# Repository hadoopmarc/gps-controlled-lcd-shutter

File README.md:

# gps-controlled-lcd-shutter

## Introduction

The GPS-controlled LCD shutter is used for photography of bright meteors. Traditionally, periodic shutters are applied in multi-station photography for aiding the calculation of the atmospheric trajectory and velocity of a meteoroid. The controlling system documented in this git repository adds 1 Hz time markers to the waveform driving an LCD shutter. These markers are synchronized with the highly accurate time signal of a GPS module. The markers function as additional reference points for comparing records from multiple stations. The technique was pioneered by the Ondřejov Observatory in the Czech Republic, see: [https://link.springer.com/article/10.1007/s11038-017-9511-z](https://link.springer.com/article/10.1007/s11038-017-9511-z).

The required pattern for obstructing the light passing through the camera lens is visible from the photograph below (courtesy of the Astronomical Institute of the Academy of Sciences of the Czech Republic).

## Reference design

When using an LCD shutter to realize the required pattern one needs an LCD opaqueness waveform represented as signal I in the figure below. The end of a long part of the meteor trail - or the rising edge of the first pulse of a pulse train in signal I - occurs a N + 2/32 seconds exactly.

The waveform required to drive the LCD shutter has both a 16 Hz signature for the periodic interruptions and a 1 Hz signature for the second markers. The Ublox Neo-M8T SoC is able to deliver both signals with high precision on its TIMEPULSE and TIMEPULSE2 outputs (signals A and B). Because of this high precision, the design with Neo-M8T is designated as the reference design.

Apart from the frequencies involved, there are additional requirements for driving an LCD shutter:

- although an LCD shutter becomes opaque when a voltage is put on it in either direction, it is advised to change the polarity of the applied voltage with each cycle to avoid degradation of the display (signal H)
- upon switching, the shutter draws a relatively high peak current of 28 mA during a short time

These requirements make that the LCD-shutter is better not driven by logical outputs directly. Rather, the reference design applies opamps to convert the logical signals into +/- 12V with a sufficiently low output impedance, see the top part of the electronic circuit below. The final opamp adds the inverted signal F to the signal G to create signal H. The electronic circuit for the final opamp includes a variable resistor RV1 to set the "inactive" output voltage to exactly 0V for maximum transparency of the LCD shutter.

For converting signals A and B into signals F and G, a few CMOS NAND ports and a D-flipflop are applied. Note that the 1 Hz signal is also fed into the reset port of the flipflop to have the edges of the 8 Hz signals D and E coincide with the rising edge of the 1 Hz signal.

## Optimized design

Although the reference design guarantees a high timing precision, it has significant drawbacks:

- the Neo-M8T is 10 times more expensive than its more nimble Neo-M8N sibling and dominates the production costs of the system
- the Neo-M8T is not available on a breakout board with the TIMEPULSE and TIMEPULSE2 output signals, so this requires high-precision soldering on 1 mm spaced SMD output pins
- the opamp circuit requires positive and negative power supplies
- the opamp circuit is hard to get stable and can only barely supply the peak current of the LCD shutter

Presenting the reference design to two different audiences resulted in valuable feedback to optimize the design:

- the required waveforms can also be produced by a microcontroller such as the Arduino board, by only using the 1 Hz output signal of a GPS module and using the internal, less precise clock of the microcontroller to obtain the 16 Hz timing information (see [this contribution to the repository](https://github.com/hadoopmarc/gps-controlled-lcd-shutter/commit/29299f46e7cd1bd2d8dd73f03644191cccfc6193)). Now, the cheaper Neo-M8N suffices to provide the 1 Hz timing data.
- an H-bridge module - often used to drive a DC motor - seems also suitable to drive the LCD shutter. An H-bridge only requires a positive power supply and can deliver high output currents.

This feedback resulted in the final optimized design, displayed in the electronic circuit diagram below. As the LCD shutter is already driven with a 16 Hz frequency, the H-bridge PWM duty cycle has a fixed setting of 100%. An H-bridge has two modes for a low output voltage, see the truth table below: short circuit the output pins ("Short brake" in motor terms) or disconnect the output pins ("Free run until frictional stop" in motor terms). It turns out that the LCD shutter needs the short circuit so that it can release its internal charge/polarity and become transparent as fast as possible.

The required input signals to the H-bridge are displayed in the waveform diagram below. Also in this design, the end of a long segment in the meteor trail - or the rising edge of the first pulse of a pulse train in the LCD opacity signal - occurs a N + 2/32 seconds exactly. After all, the long segment in the meteor trail has a duration of 3/32 second, but the GPS second pulse occurs after 1/32 second from the start of the long segment.

## Validation of the designs

Proper operation of both designs can be validated with an [Arduino Oscilloscope](./doc/arduino-scope.md) and the small LED + phototransistor setup of the lower left part of the electronic circuit diagram.

The two oscilloscope diagrams above display signals F and G (yellow lines) simultaneously measured with the Pulse Per Second signal of the Neo-M8T module  (configured with a pulse duration of 50 ms). The pulse duration of signals F and G is 46875 ms (16 Hz with a duty cycle of 75% in case of a missing GPS satellite lock). The first diagram shows that the pulse at the start of a second is missing, as required.

In this image the yellow line represents the light throughput of the LCD shutter while driven by the reference design. The light is interrupted (sharp falling edges) at the start of a driver pulse (pulses not visible). There is no sharp falling edge coinciding with the rising edge of the GPS Pulse Per Second signal and the shutter can fully open. Note that these measurements were made with the cheap first generation LC-TEC shutters and that the measured opening response is consistent with [Figure 8.6 of their specifications](https://www.lc-tec.se/wp-content/uploads/2019/05/FOS_FOS-AR-specification-1602.pdf). Also note that the light transmission of the odd and even pulses is not exactly equal, indicating that the opamp driver circuit is not exactly balanced.

Again the light throughput against the GPS Pulse Per Second signal, but now for the optimized design with a Neo-M8N GPS module, an Arduino Nano and an H-bridge. Now, the GPS pulse has a duration of 100 ms and the duty cycle of the driver pulses is 50%, which gives the LCD-shutter more time to open than in the earlier image for the reference design.

This picture looks boring, but its significance is high. It displays the reference and optimized designs operating simultaneously with independent GPS receiver modules, both with a satellite lock. The white line shows signal F from the reference design, while the yellow line shows the H-bridge IN1 signal of the optimized design. This demonstrates that within the measuring accuracy of the oscilloscope used, the edges of the signals coincide.

This picture is a more attractive-looking variation on the picture above, again combining measurements from two independently operating setups. Here, signal F from the reference design (white line) is combined with the light throughput of the LCD shutter driven by the optimized design (yellow line). Also, here the opening and closing instances of the LCD-shutter nicely coincide with the falling and rising edges of signal F. Note that the measurements in the last two images were made with the electronic circuits built on a printed circuit board, while previous more noisy images were from circuits built on a breadboard. Also, a different phototransistor and LCD-shutter were used, explaining the slightly different light throughput curve, compared to the earlier images.

Starting from version 0.2.0 the electrical shut percentage can be configured to compensate for LCD shutters that fail to reopen fast enough to truthfully follow the electrical signals. In this oscilloscope screenshot a shut percentage of 25% is applied to a cheap LCD shutter, resulting in an open/closed ratio of roughly 50/50. White line is the GPS signal.

## Phase measurements in the optimized design

Apart from validation measurements of the output signals of the electronic circuits, it is also possible to use internal measurements from the microcontroller as a form of validation. The controlling software generates the pulses using timer interrupts. The timer period is chosen such that the end of a pulse train occurs at a phase difference Δt just before the ideal time instance required by the nanosecond precision GPS time. For an Arduino Nano microcontroller the timer has a limited resolution and as a result Δt has a stable value between 0 and 128 microseconds. How to monitor this phase difference and phase stability is described [here](./doc/arduino-programming.md).

## Further documentation

- [Programming the Arduino Nano module](./doc/arduino-programming.md)
- [Measuring with an Arduino Oscilloscope](./doc/arduino-scope.md)
- [Datasheets of system components](./doc/datasheet.md)

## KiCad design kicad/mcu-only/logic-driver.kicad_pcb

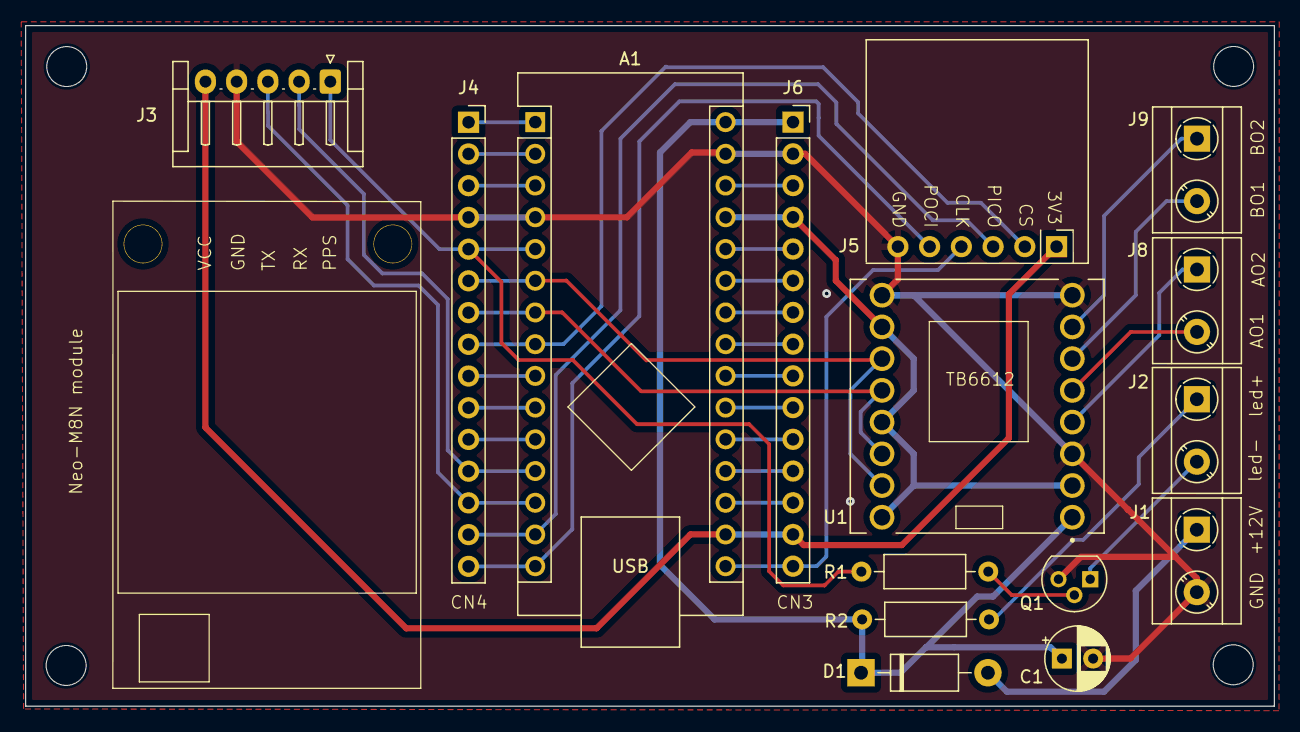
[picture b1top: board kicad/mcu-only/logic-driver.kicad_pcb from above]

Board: 2 copper layers, 100.0 x 54.5 mm, 19 parts (0 on the bottom side), 37 nets.

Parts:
A1: STM32G431 / Arduino Nano; Arduino_Nano
C1: 47uF; CP_Radial_D5.0mm_P2.50mm
D1: 1N5818; D_DO-41_SOD81_P10.16mm_Horizontal
H1, H2, H3, H4: Hole; MountingHole_3.2mm_M3_ISO14580
J1: 12V/1A power in; TerminalBlock_RND_1x02_P5.00mm_Horizontal_Small_Courtyard
J2: PPS; TerminalBlock_RND_1x02_P5.00mm_Horizontal_Small_Courtyard
J3: Onboard Neo_M8N; Neo-M8N_1x05_P2.50mm_Horizontal
J4: CN4; PinSocket_1x15_P2.54mm_Vertical
J5: Onboard SD-card; SDcard_IPC_breakout_1x06_P2.54mm_Vertical
J6: CN3; PinSocket_1x15_P2.54mm_Vertical
J8: LCD-A; TerminalBlock_RND_1x02_P5.00mm_Horizontal_Small_Courtyard
J9: LCD-B; TerminalBlock_RND_1x02_P5.00mm_Horizontal_Small_Courtyard
Q1: BC547; TO-92
R1: 47k; R_Axial_DIN0207_L6.3mm_D2.5mm_P10.16mm_Horizontal
R2: 1k5; R_Axial_DIN0207_L6.3mm_D2.5mm_P10.16mm_Horizontal
U1: ROB-14450; TB6612_Module_ROB-14450

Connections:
/+12V: A1.30 (VIN), C1.1, D1.1 (K), J6.1, R2.1, U1.1 (VM)
/AVDD: A1.18 (AREF), J6.13
/MCU_3V3: A1.17 (3V3), J3.5, J5.1, J6.14
/MCU_5V: A1.27 (+5V), J6.4, U1.2 (VCC), U1.10 (PWMB), U1.13 (STBY), U1.16 (PWMA)
/NRSTA: A1.3 (~RESET), J4.3
/NRSTB: A1.28 (~RESET), J6.3
/PA0: A1.19 (A0), J6.12
/PA1: A1.20 (A1), J6.11
/PA2: A1.26 (A7), J6.5
/PA3: A1.21 (A2), J6.10
/PA4: A1.22 (A3), J6.9
/PA5/PB7: A1.23 (SDA/A4), J6.8
/PA6/PA15: A1.24 (SCL/A5), J6.7
/PA7: A1.25 (A6), J6.6
/PA8: A1.12 (D9), J3.2, J4.12
/PA9: A1.1 (TX1), J4.1
/PA10: A1.2 (RX1), J4.2
/PA11: A1.13 (D10), J3.3, J4.13
/PA12: A1.5 (D2), J3.1, J4.5, R1.1
/PA15: A1.8 (D5), J4.8, J5.2
/PB0: A1.6 (D3), J4.6, U1.11 (BI2), U1.15 (AI2)
/PB3/PB8: A1.16 (SCK), J5.4, J6.15
/PB4: A1.15 (MISO), J4.15, J5.5
/PB5: A1.14 (MOSI), J4.14, J5.3
/PB6: A1.9 (D6), J4.9
/PB7: A1.7 (D4), J4.7, U1.12 (BI1), U1.14 (AI1)
/PF0: A1.10 (D7), J4.10
/PF1: A1.11 (D8), J4.11
GND: A1.4 (GND), A1.29 (GND), C1.2, J1.2, J3.4, J4.4, J5.6, J6.2, Q1.3 (E), U1.3 (GND), U1.8 (GND), U1.9 (GND)
unnamed: D1.2 (A), J1.1
unnamed: J2.1, R2.2
unnamed: J2.2, Q1.1 (C)
unnamed: J8.1, U1.4 (A01)
unnamed: J8.2, U1.5 (A02)
unnamed: J9.1, U1.7 (B01)
unnamed: J9.2, U1.6 (B02)
unnamed: Q1.2 (B), R1.2

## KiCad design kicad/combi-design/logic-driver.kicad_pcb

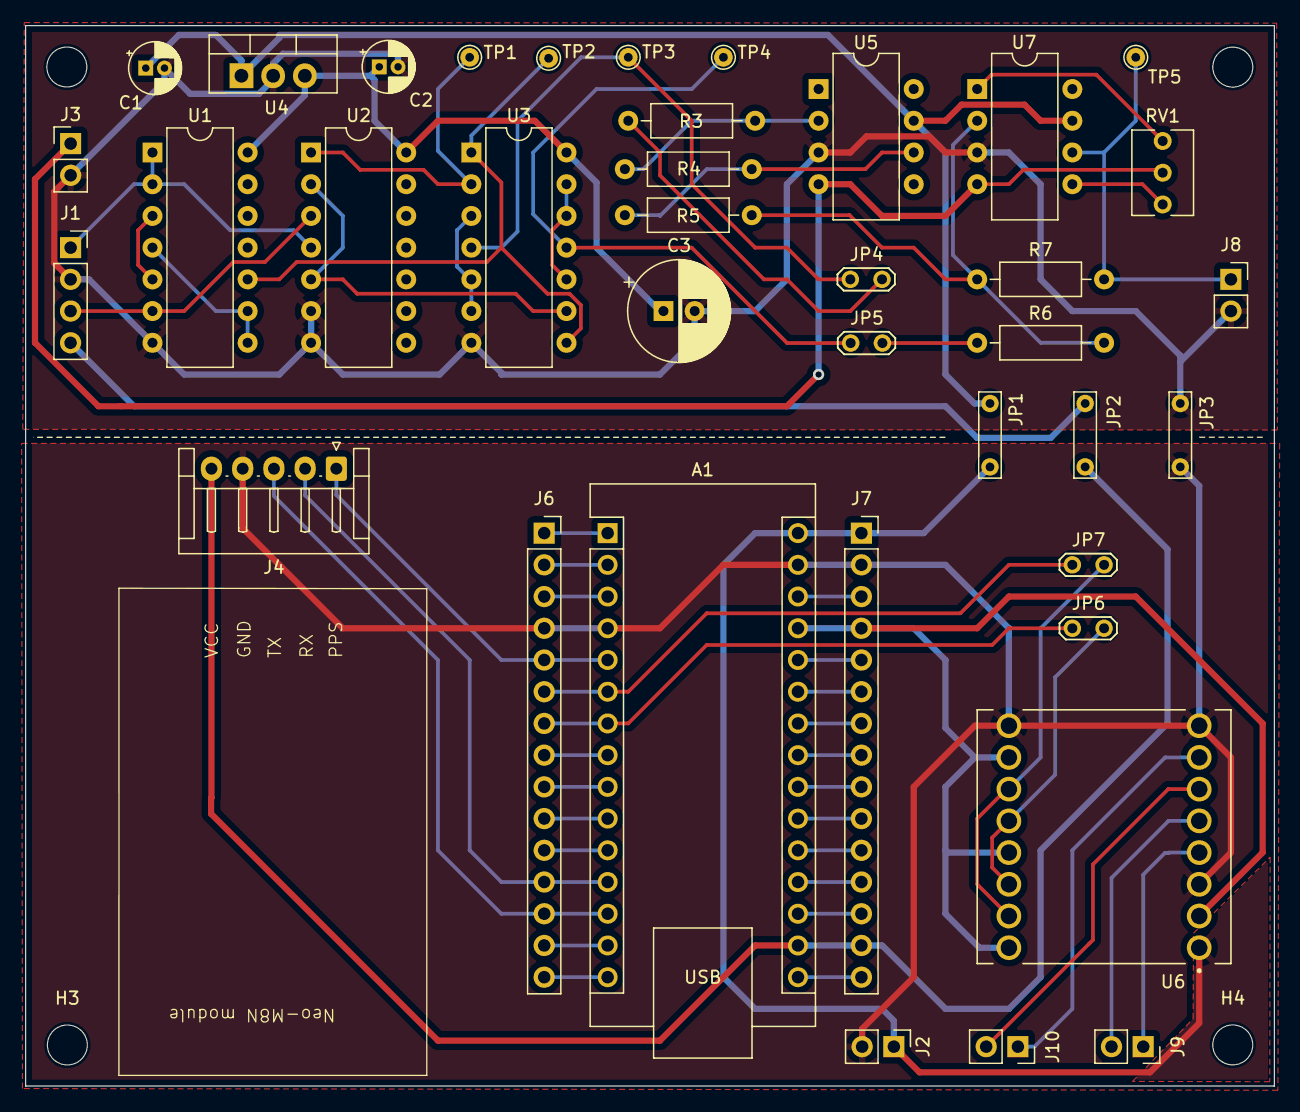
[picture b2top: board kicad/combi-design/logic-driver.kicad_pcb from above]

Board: 2 copper layers, 100.0 x 84.9 mm, 42 parts (0 on the bottom side), 59 nets.

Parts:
A1: Nucleo32-STM32G431; Arduino_Nano
C1, C2: 2.2uF; CP_Radial_D4.0mm_P1.50mm
C3: 100uF; CP_Radial_D8.0mm_P2.50mm
H1, H2, H3, H4: MountingHole; MountingHole_3.2mm_M3_ISO14580
J1: Neo-M8T; PinSocket_1x04_P2.54mm_Vertical
J2, J3: Power in; PinHeader_1x02_P2.54mm_Vertical
J4: Onboard Neo_M8N; Neo-M8N_1x05_P2.50mm_Horizontal
J6: CN4; PinSocket_1x15_P2.54mm_Vertical
J7: CN3; PinSocket_1x15_P2.54mm_Vertical
J8: LCD-opamp; PinSocket_1x02_P2.54mm_Vertical
J9: LCD-A; PinSocket_1x02_P2.54mm_Vertical
J10: LCD-B; PinSocket_1x02_P2.54mm_Vertical
JP1: +12V; TestPoint_Bridge_Pitch5.08mm_Drill0.7mm
JP2: +3V3; TestPoint_Bridge_Pitch5.08mm_Drill0.7mm
JP3: GND; TestPoint_Bridge_Pitch5.08mm_Drill0.7mm
JP4, JP6: Pos pulses; TestPoint_2Pads_Pitch2.54mm_Drill0.8mm
JP5, JP7: Neg pulses; TestPoint_2Pads_Pitch2.54mm_Drill0.8mm
R3, R4, R5, R6, R7: 100k; R_Axial_DIN0207_L6.3mm_D2.5mm_P10.16mm_Horizontal
RV1: 100k; Potentiometer_Vishay_T73XW_Horizontal
TP1: Signal D; TestPoint_THTPad_D1.5mm_Drill0.7mm
TP2: Signal C; TestPoint_THTPad_D1.5mm_Drill0.7mm
TP3: Signal F; TestPoint_THTPad_D1.5mm_Drill0.7mm
TP4: Signal G; TestPoint_THTPad_D1.5mm_Drill0.7mm
TP5: Signal H; TestPoint_THTPad_D1.5mm_Drill0.7mm
U1, U3: 4011; CERDIP-14_W7.62mm_SideBrazed
U2: 4013; CERDIP-14_W7.62mm_SideBrazed
U4: LM7805_TO220; TO-220-3_Vertical
U5, U7: TL081; CERDIP-8_W7.62mm_SideBrazed
U6: ROB-14450; TB6612_Module_ROB-14450

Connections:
+L12V: C1.1, JP1.2 (B), U4.1 (VI), U5.7 (V+), U7.7 (V+)
-L12V: J3.1, RV1.2, U5.4 (V-), U7.4 (V-)
/+5V: C2.1, C3.1, U1.14 (VDD), U2.14 (VDD), U3.14 (VDD), U4.3 (VO)
/+12V: A1.30 (VIN), J2.1, J7.1, JP1.1 (A), U6.1 (VM)
/AVDD: A1.18 (AREF), J7.13
/L3V3: J1.4, JP2.2 (B)
/LGND: C1.2, C2.2, C3.2, J1.2, J3.2, J8.2, JP3.2 (B), U1.7 (VSS), U2.6 (S), U2.7 (VSS), U3.7 (VSS), U4.2 (GND), U5.3 (+), U7.3 (+)
/MCU_3V3: A1.17 (3V3), J4.5, J7.14, JP2.1 (A)
/MCU_5V: A1.27 (+5V), J7.4, U6.2 (VCC), U6.10 (PWMB), U6.13 (STBY), U6.16 (PWMA)
/NRSTA: A1.3 (~RESET), J6.3
/NRSTB: A1.28 (~RESET), J7.3
/PA0: A1.19 (A0), J7.12
/PA1: A1.20 (A1), J7.11
/PA2: A1.26 (A7), J7.5
/PA3: A1.21 (A2), J7.10
/PA4: A1.22 (A3), J7.9
/PA5/PB7: A1.23 (SDA/A4), J7.8
/PA6/PA15: A1.24 (SCL/A5), J7.7
/PA7: A1.25 (A6), J7.6
/PA8: A1.12 (D9), J4.2, J6.12
/PA9: A1.1 (TX1), J6.1
/PA10: A1.2 (RX1), J6.2
/PA11: A1.13 (D10), J4.3, J6.13
/PA12: A1.5 (D2), J4.1, J6.5
/PA15: A1.8 (D5), J6.8
/PB0: A1.6 (D3), J6.6, JP7.1 (A)
/PB3/PB8: A1.16 (SCK), J7.15
/PB4: A1.15 (MISO), J6.15
/PB5: A1.14 (MOSI), J6.14
/PB6: A1.9 (D6), J6.9
/PB7: A1.7 (D4), J6.7, JP6.1 (A)
/PF0: A1.10 (D7), J6.10
/PF1: A1.11 (D8), J6.11
GND: A1.4 (GND), A1.29 (GND), J2.2, J4.4, J6.4, J7.2, JP3.1 (A), U6.3 (GND), U6.8 (GND), U6.9 (GND)
unnamed: J1.1, U1.1, U1.2, U2.4 (R)
unnamed: J1.3, U1.6, U2.3 (C)
unnamed: J8.1, R7.2, TP5.1, U7.6
unnamed: J9.1, U6.4 (A01)
unnamed: J9.2, U6.5 (A02)
unnamed: J10.1, U6.7 (B01)
unnamed: J10.2, U6.6 (B02)
unnamed: JP4.1 (A), TP3.1, U3.4
unnamed: JP4.2 (B), R3.1
unnamed: JP5.1 (A), TP4.1, U3.11
unnamed: JP5.2 (B), R6.1
unnamed: JP6.2 (B), U6.12 (BI1), U6.14 (AI1)
unnamed: JP7.2 (B), U6.11 (BI2), U6.15 (AI2)
unnamed: R4.2, R5.1, U5.6
unnamed: RV1.1, U7.1 (NULL)
unnamed: RV1.3, U7.5 (NULL)
unnamed: TP2.1, U1.10, U3.1, U3.8
unnamed: U1.3, U1.5
unnamed: U1.4, U1.8, U1.9
unnamed: U2.2 (~Q), U2.5 (D), U3.9
unnamed: TP1.1, U2.1 (Q), U3.2
unnamed: U3.3, U3.5, U3.6
unnamed: U3.10, U3.12, U3.13
unnamed: R3.2, R4.1, U5.2 (-)
unnamed: R5.2, R6.2, R7.1, U7.2 (-)

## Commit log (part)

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2023-11-28 Adds initial documentation and placeholder for Arduino script
2023-12-12 Added a script to generate the waveform
2023-12-12 just noticed it was supposed to be 16, not 32Hz
2023-12-13 Fixed the period being clipped to an int
    The period was being calculated as 62 instead of 62.5, resulting
    in subtle timing errors.
2023-12-28 Adds documentation on Neo-M8T configuration
2023-12-28 Fixes table rendering on github, first attempt
2023-12-28 Fixes table rendering on github, 2nd attempt
2023-12-28 Corrects 75% pulse duration without satfix
2023-12-29 Adds ublox config save command and some datasheets
2024-01-12 Rewires the D-flipflop divider to have signal C in phase with TIMEPULSE
2024-01-12 Puts arduino file in folder
2024-01-12 Adds Arduino oscilloscope files
2024-02-04 Adds two images
2024-02-04 Improves oscilloscope display
2024-02-04 Adds datasheet links
2024-02-17 Updates the electronic schema
2024-03-10 Adds unfinished Arduino R4 script for slow 3-level waveform on A0 DAC output
2024-03-10 Adds Arduino slow waveform with two dig outputs; still without timers
2024-03-17 Adds arduino script for measuring loop jitter
2024-03-22 Adds new Arduino test waveforms for attempts on faster opening the LCD-shutter
2024-04-01 Redesigns the main two-pin waveform, still with errors but promising
2024-04-08 Completes accurate waveform using two of three mechanisms
2024-04-13 Update schema regarding voltage follower
2024-05-05 Improves two pin waveform regarding stability and consistency
2024-05-05 Fixes logic error when to increment the iHalfWave counter
2024-05-09 Adds script for driving an H-bridge
2024-05-25 Adds rened kicad circuit and the kicad PCB design
2024-05-25 Updates electric circuit diagram
2024-06-08 Add documentation for programming the Arduino
2024-06-23 Adds documentation for measuring with the Arduino oscilloscope script
2024-06-29 Fixes overflow issue
2024-06-29 Updates arduino docs with the changed figures
2024-06-29 Fixes second marker for new iGpsPulse semantics + cleaning up
2024-06-29 Adds preliminary calibration after 10 seconds of stabilization
2024-06-29 Updates Arduino programming docs
2024-08-16 Adds reference design documentation
2024-08-25 Reorganizes arduino folder
2024-08-25 Adds sdfat exploration example for using long file names
2024-08-25 Extends sdfat exploration example with creating a file
2024-09-01 Adds Arduino code for GPS time + latlon readout
2024-10-05 Changes comments only
2024-10-05 Adds blinking LED script
2024-10-09 Adds KiCAD design files for the mcu-only PCB
2024-10-13 Updates documentation mcu-only
2024-10-18 Introduces additional INIT state and prints VERSION
2024-10-19 Restructures code to decrease complexity and avoid unwanted lock states
2024-10-19 Fixes chipselect pin for AliExpress SD card reader
2024-10-20 Adds compemsation for code execution time and tunes parameters
2024-10-20 Updates the documentation on phase locking
2024-10-25 Makes first attempt to add duty cycle but has shutter open two timer per second
2024-10-25 Rebases block2080 and makes SHUT_PERCENTAGE a #define in the .ino file
2024-11-09 Fixes remaining logical errors in the 20/80 design
2024-11-09 Adds scope screenshot of succesful 25% locked state
2024-11-09 Updates the documentation for the new version
2024-12-08 Adds current status of rain sensor (arduino and buienradar)
2024-12-25 Adapts test scripts to new rainsensor shield
2024-12-27 Combines gps time and sdcard file creation in rain monitor
2024-12-27 Fixes gps time init error
2024-12-29 Writes continuous measurements to serial monitor
2024-12-29 Fixes reading date/time from GPS
2025-01-03 Writes measurements to SDcard and syncs to GPS every hour
2025-01-11 Makes test-rtc more robust
2025-02-02 Adds rain monitor script
2025-02-07 Adds GPS fix check at start of rainmonitor
2025-03-28 Makes sdfat and softwareserial libs truly independent
2025-03-28 Adds standalone Melexis test script
2025-03-29 Adds Melexis measurements
2025-04-13 Add Melexis measurements to the rainmonitor. Also adds a debug mode that starts a new log file every 5 minutes (only tested without shield)
2025-04-21 WIP temp
2025-05-04 Adds DEBUG mode that start new logfile every 5 minutes
2025-05-22 Makes monitoring script pass the 12:00 border with new SanDisk, better power supply and level shifters
2025-05-31 Adds pull-up resistors to I2C bus to Melexis
2025-06-08 Adds watchdog timer and improves output formatting
2025-06-08 Improves time loop + UTC and resubscribes MQTT on reconnect
2025-06-09 Makes timing independent of time.sleep accuracy
2025-06-09 Refactors dtostrf alternative for fixed width printed floats
2025-06-20 Merges the 2 kinds of files with measurement data
2025-06-20 Adds plots to the analysis
2025-06-21 Fixes reading of erroneously formatted t_sky values
2025-06-22 Fixes dateshift and float representations
2025-07-18 Fixes UTC calculation of online sensors
2025-08-16 Increments TESTRUN_DIR
2025-08-29 Changes to external 24H resets
2025-09-21 Fixes dtostrfixed rounding issue
2025-10-17 Adds initial rain viz app
2025-10-19 Formats the streamlit app
2025-10-26 Adds python-dotenv package
2025-10-31 Adds exception handling to buienradar requests
2025-11-02 Gets the streamlit clear sky viewer in working order
2025-11-02 Adds requirements.txt for streamlit clearsky
2025-11-08 Prepares streamlit app for dockerization
2025-11-08 Adds Dockerfile with instructions
2025-11-08 Updates instructions in clearsky Dockerfile
2026-01-03 Fixes various minor issues
2026-03-01 Adds module to download allsky images from a remote server
2026-03-15 Renames streamlit app and adds reading with wireguard
2026-03-15 FIxes past midnight times and stale images; adds download progress bar
2026-03-20 Fixes count window and adds start counts in calendar cells
2026-03-21 Adds en station image bulk downloader
2026-03-21 Prepares process_data and webapp for different EN stations
2026-03-29 Adds modeling script and various improvements to the processing pipeline
2026-04-03 Makes minor improvements to the rain data processing and web app
2026-04-11 Fixes stored images after midnight and plot styling
